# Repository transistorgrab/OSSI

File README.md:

# OSSI
Open Source Solar Inverter - Software, Hardware, Mechanics

This repository initially clones all content from the former Sourceforge hosted project site (https://sourceforge.net/projects/os-si/). Since the outages on Sourceforge became more frequent, I decided to change over to Github which seems more reliable at this time.

This project aims to build an Open Source (Software and Hardware) Solar Inverter.

The goal is to design a solar inverter with parts that are available trough common distributors with no special manufactured parts.

All documentation (software, hardware, mechanics) is open and free to use by everyone.

Solar inverters can be very complex devices to build and there is a lot to learn on the way.

Join, collaborate, learn and help make the world a better place.

The sun shines for everyone! 😊

The current activities take place in the [Wiki](https://github.com/transistorgrab/OSSI/wiki), where we collect the requirements.

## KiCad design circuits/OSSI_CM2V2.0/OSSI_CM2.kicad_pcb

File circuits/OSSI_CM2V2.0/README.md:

# O.S.S.I Control Module 2 V2.0

This version of the control module contains various improvements over version 1.0/1.1 of the module.

## Breaking Changes
### Different controller pin mapping.
This change was necessary due to an oversight when assigning pins to PWMs. Now the bridge controlling PWMs are assigned to timer 1 channel 1 and 1N and channels 2 and 2N which now implements requirement SOFT-3002.

However, the module footprint still shows the same pin mapping as before.

## Improvements
The board now features an I²C EEPROM for storage of parameters, settings, counters and other data that should be protected between firmware updates. This is an actual EEPROM and not a Flash due to vastly better data retention and write cycles.

The package of the 8 pin ICs on the module are now changed to TSSOP to improve use of board space.

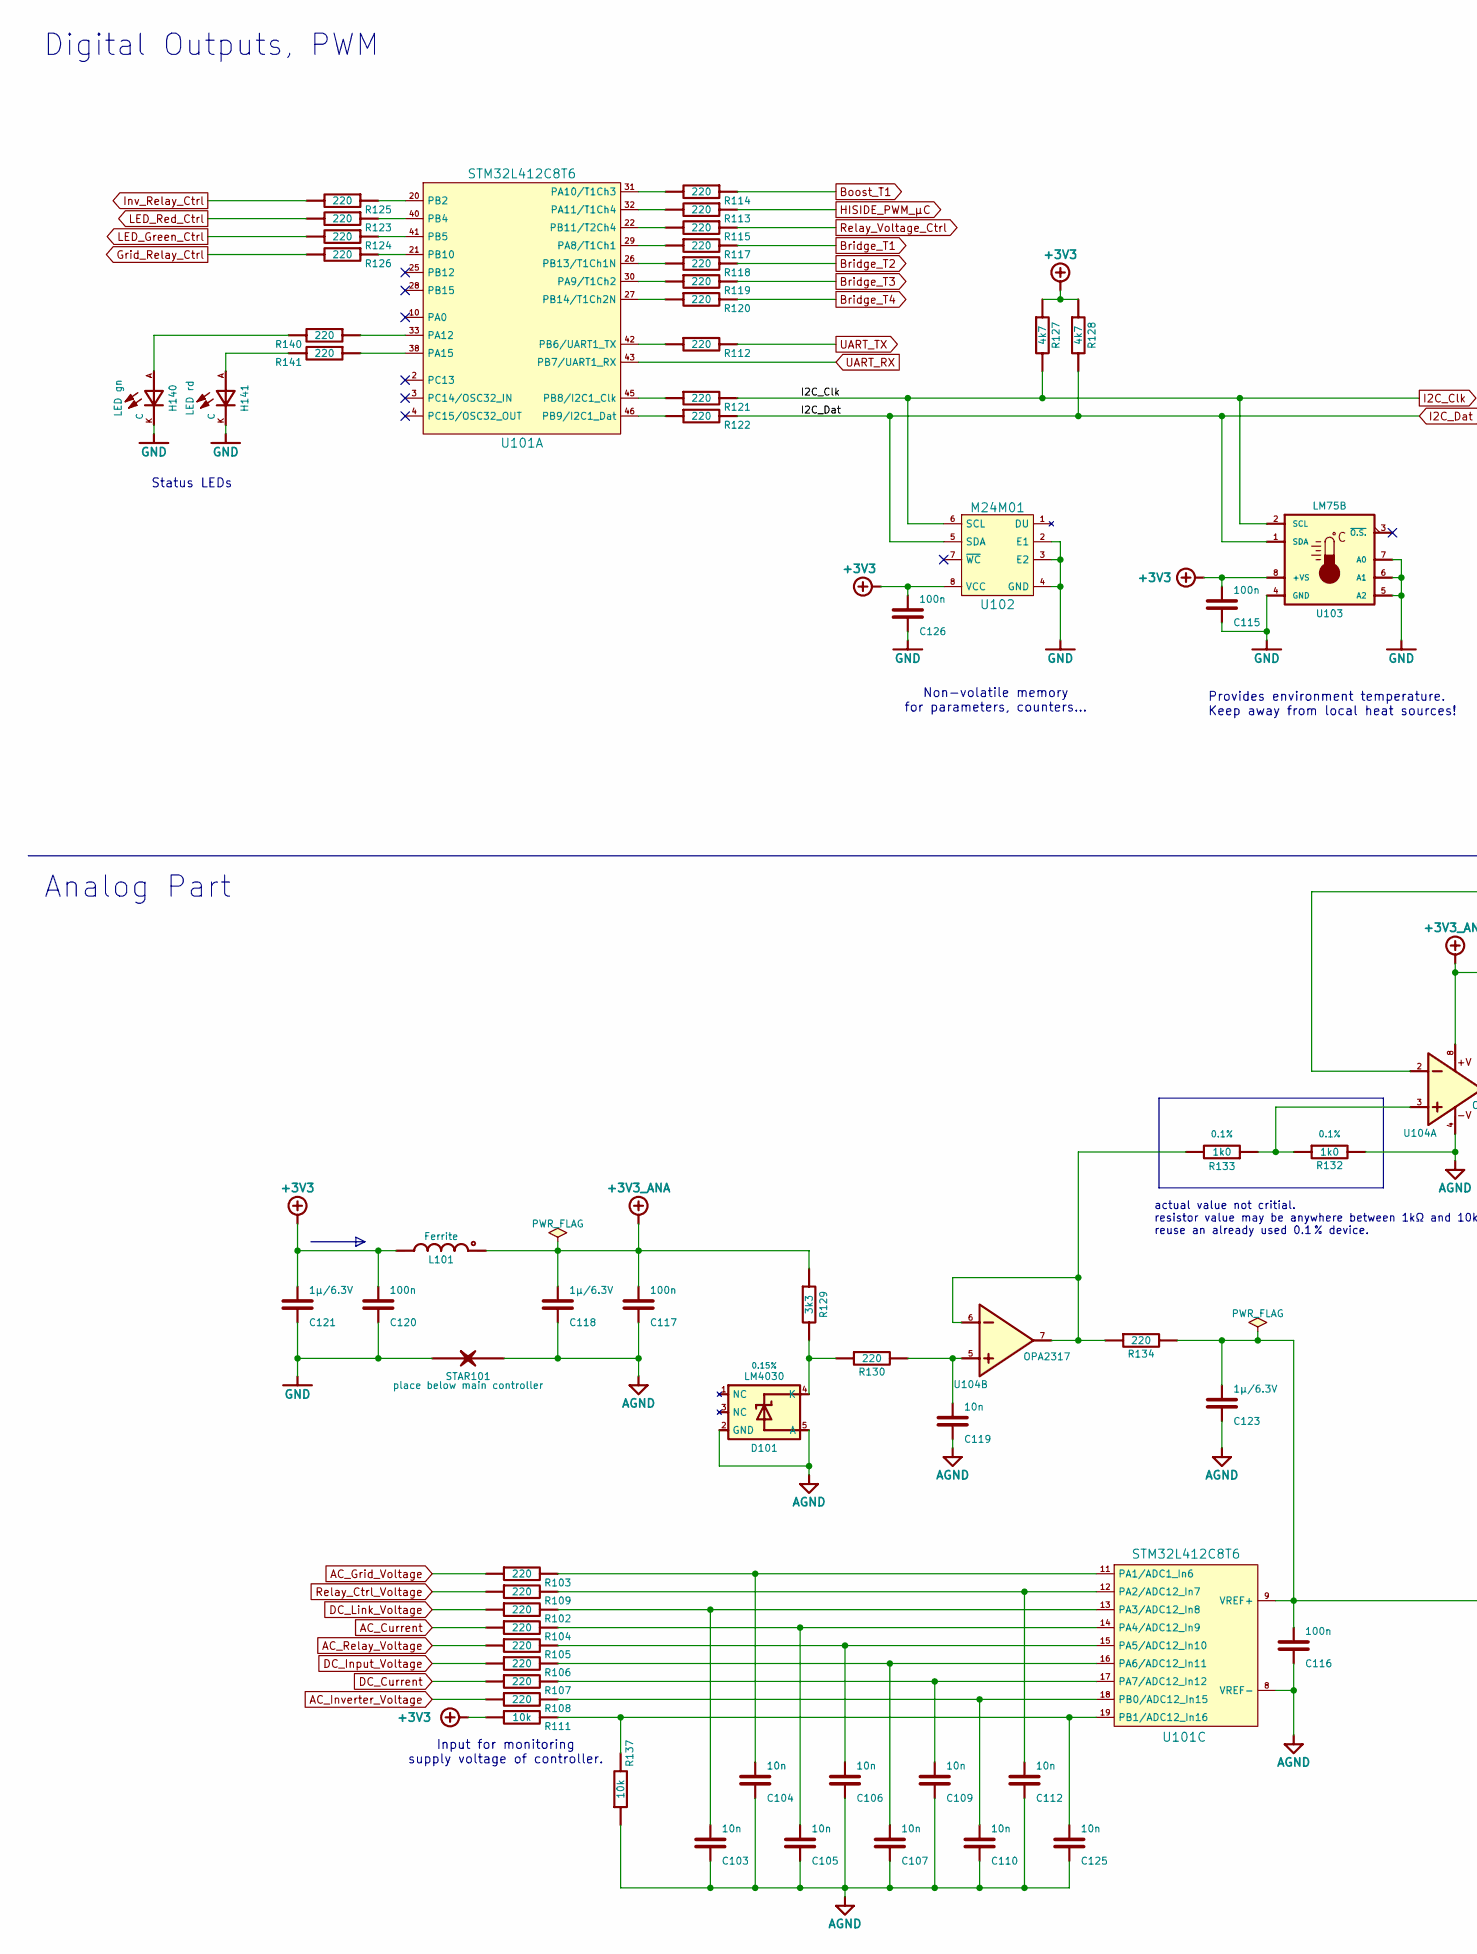
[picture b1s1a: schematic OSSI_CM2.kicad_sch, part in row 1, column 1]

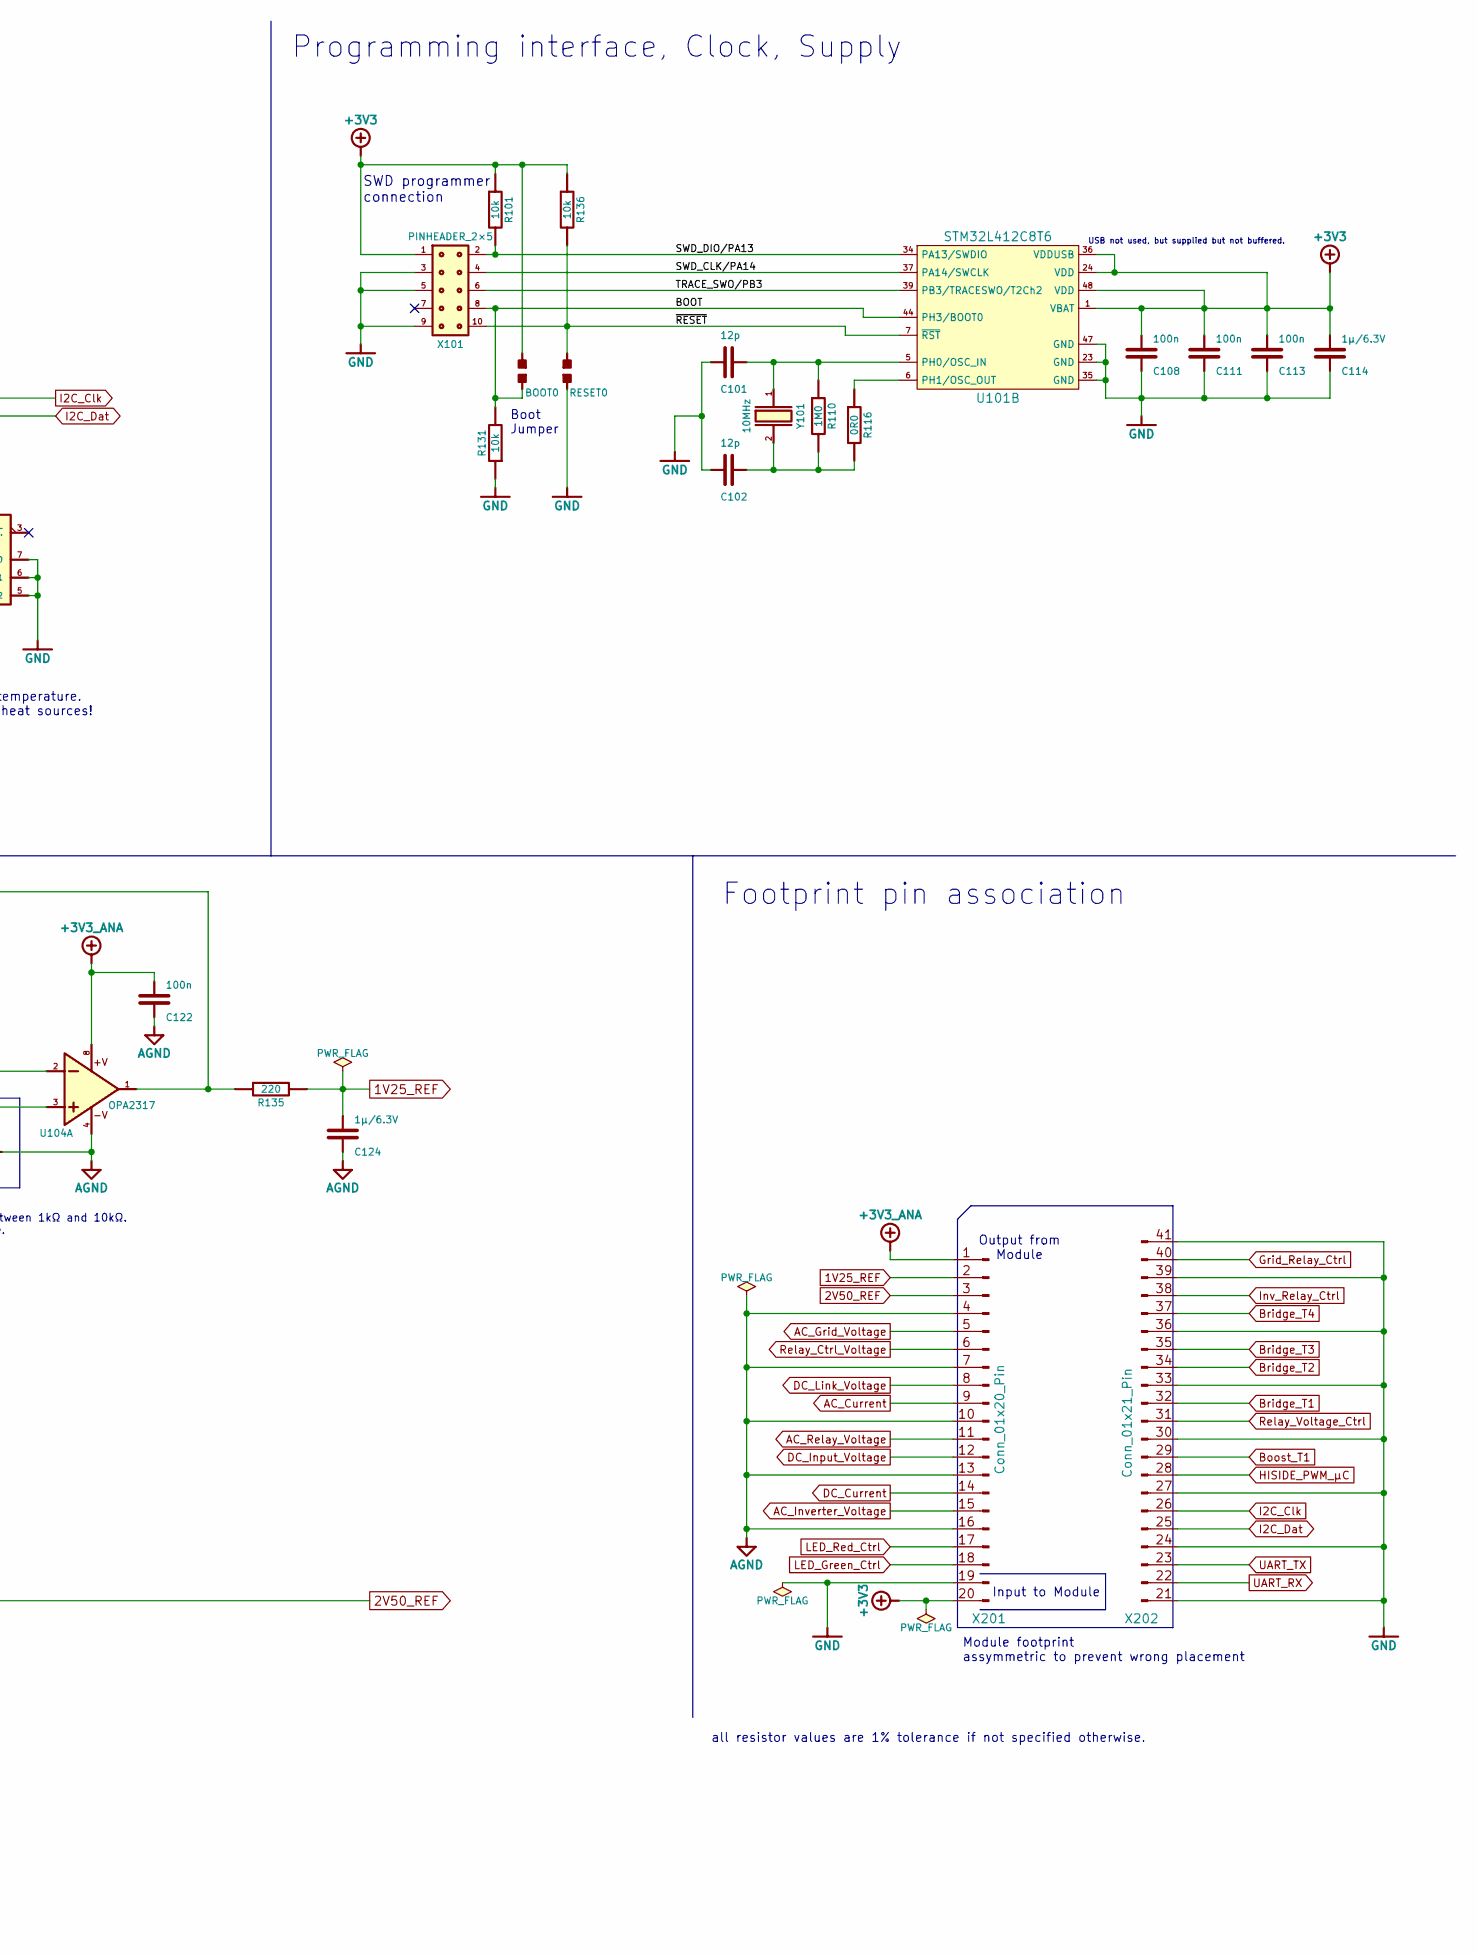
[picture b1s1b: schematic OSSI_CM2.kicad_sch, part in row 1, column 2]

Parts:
BOOT0: Solder_bridge_open; JUMPER_OPEN
C101, C102: 12p; 0603_W_C; Tolerance %; Partnumber P
C103, C104, C105, C106, C107, C109, C110, C112, C119, C125: 10n; 0603_W_C; Tolerance %; Partnumber P
C108, C111, C113, C115, C116, C117, C120, C122, C126: 100n; 0603_W_C; Tolerance %; Partnumber P
C114, C118, C121, C123, C124: 1µ/6.3V; 0805_W_C; Tolerance %; Partnumber P
D101: LM4030; SOT-23-5; Tolerance 0.15%; Partnumber P
H140: LED gn; 0603_W_LED; Partnumber P
H141: LED rd; 0603_W_LED; Partnumber P
L101: Ferrite; 0805_W_L; Partnumber P
R101, R111, R131, R136, R137: 10k; 0603_W_R; Tolerance %; Partnumber P
R102, R103, R104, R105, R106, R107, R108, R109, R112, R113, R114, R115, R117, R118, R119, R120, R121, R122, R123, R124, R125, R126, R130, R134, R135, R140, R141: 220; 0603_W_R; Tolerance %; Partnumber P
R110: 1M0; 0603_W_R; Tolerance %; Partnumber P
R116: 0R0; 0603_W_R; Tolerance %; Partnumber P
R127, R128: 4k7; 0603_W_R; Tolerance %; Partnumber P
R129: 3k3; 0603_W_R; Tolerance %; Partnumber P
R132, R133: 1k0; 0603_W_R; Tolerance 0.1%; Partnumber P
RESET0: Solder_bridge_open; JUMPER_OPEN
STAR101: STARPOINT
U101: STM32L412C8T6; LQFP-48_7x7mm_P0.5mm
U102: M24M01; TSSOP8
U103: LM75B; TSSOP8
U104: OPA2317; TSSOP8; Partnumber P
X101: PINHEADER_2×5; PinHeader_2x05_P2.54mm_Vertical; Partnumber P
X201: Conn_01x20_Pin; PinHeader_1x20_P2.54mm_Vertical
X202: Conn_01x21_Pin; PinHeader_1x21_P2.54mm_Vertical
Y101: 10MHz; HC49_US; Partnumber P

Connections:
1V25_REF: C124.2, R135.2, X201.2
2V50_REF: C116.2, C123.2, R134.2, U101.9 (VREF+), X201.3
+3V3: BOOT0.1, C108.2, C111.2, C113.2, C114.2, C115.2, C120.2, C121.2, C126.2, L101.2, R101.1, R111.1, R127.1, R128.1, R136.1, U101.1 (VBAT), U101.24 (VDD), U101.36 (VDDUSB), U101.48 (VDD), U102.8 (VCC), U103.8 (+VS), X101.1, X201.20
+3V3_ANA: C117.2, C118.2, C122.2, L101.1, R129.1, U104.8, X201.1
/BOOT: BOOT0.2, R131.2, U101.44 (PH3/BOOT0), X101.8
/SWD_CLK/PA14: U101.37 (PA14/SWCLK), X101.4
/SWD_DIO/PA13: R101.2, U101.34 (PA13/SWDIO), X101.2
/TRACE_SWO/PB3: U101.39 (PB3/TRACESWO/T2Ch2), X101.6
/~RESET: R136.2, RESET0.2, U101.7 (~RST), X101.10
AC_Current: R104.1, X201.9
AC_Grid_Voltage: R103.1, X201.5
AC_Inverter_Voltage: R108.1, X201.15
AC_Relay_Voltage: R105.1, X201.11
AGND: C103.1, C104.1, C105.1, C106.1, C107.1, C109.1, C110.1, C112.1, C116.1, C117.1, C118.1, C119.1, C122.1, C123.1, C124.1, C125.1, D101.2 (GND), D101.5 (A), R132.2, R137.1, STAR101.1, U101.8 (VREF-), U104.4, X201.4, X201.7, X201.10, X201.13, X201.16
Boost_T1: R114.1, X202.29
Bridge_T1: R117.2, X202.32
Bridge_T2: R118.2, X202.34
Bridge_T3: R119.2, X202.35
Bridge_T4: R120.2, X202.37
DC_Current: R107.1, X201.14
DC_Input_Voltage: R106.1, X201.12
DC_Link_Voltage: R102.1, X201.8
GND: C101.1, C102.1, C108.1, C111.1, C113.1, C114.1, C115.1, C120.1, C121.1, C126.1, H140.K, H141.K, R131.1, RESET0.1, STAR101.2, U101.23 (GND), U101.35 (GND), U101.47 (GND), U102.2 (E1), U102.3 (E2), U102.4 (GND), U103.4 (GND), U103.5 (A2), U103.6 (A1), U103.7 (A0), X101.3, X101.5, X101.9, X201.19, X202.21, X202.24, X202.27, X202.30, X202.33, X202.36, X202.39, X202.41
Grid_Relay_Ctrl: R126.2, X202.40
HISIDE_PWM_µC: R113.1, X202.28
I2C_Clk: R121.2, R127.2, U102.6 (SCL), U103.2 (SCL), X202.26
I2C_Dat: R122.2, R128.2, U102.5 (SDA), U103.1 (SDA), X202.25
Inv_Relay_Ctrl: R125.2, X202.38
LED_Green_Ctrl: R124.2, X201.18
LED_Red_Ctrl: R123.2, X201.17
unnamed: C102.2, R110.2, R116.2, Y101.2
unnamed: C119.2, R130.2, U104.5
unnamed: D101.4 (K), R129.2, R130.1
unnamed: H140.A, R140.2
unnamed: H141.A, R141.2
unnamed: R132.1, R133.1, U104.3
unnamed: R133.2, R134.1, U104.6, U104.7
unnamed: R135.1, U104.1, U104.2
unnamed: R117.1, U101.29 (PA8/T1Ch1)
unnamed: R119.1, U101.30 (PA9/T1Ch2)
unnamed: R114.2, U101.31 (PA10/T1Ch3)
unnamed: R113.2, U101.32 (PA11/T1Ch4)
unnamed: R140.1, U101.33 (PA12)
unnamed: R141.1, U101.38 (PA15)
unnamed: R125.1, U101.20 (PB2)
unnamed: R123.1, U101.40 (PB4)
unnamed: R124.1, U101.41 (PB5)
unnamed: R112.1, U101.42 (PB6/UART1_TX)
unnamed: R121.1, U101.45 (PB8/I2C1_Clk)
unnamed: R122.1, U101.46 (PB9/I2C1_Dat)
unnamed: R126.1, U101.21 (PB10)
unnamed: R115.2, U101.22 (PB11/T2Ch4)
unnamed: R118.1, U101.26 (PB13/T1Ch1N)
unnamed: R120.1, U101.27 (PB14/T1Ch2N)
unnamed: C101.2, R110.1, U101.5 (PH0/OSC_IN), Y101.1
unnamed: R116.1, U101.6 (PH1/OSC_OUT)
unnamed: C104.2, R103.2, U101.11 (PA1/ADC1_In6)
unnamed: C112.2, R109.2, U101.12 (PA2/ADC12_In7)
unnamed: C103.2, R102.2, U101.13 (PA3/ADC12_In8)
unnamed: C105.2, R104.2, U101.14 (PA4/ADC12_In9)
unnamed: C106.2, R105.2, U101.15 (PA5/ADC12_In10)
unnamed: C107.2, R106.2, U101.16 (PA6/ADC12_In11)
unnamed: C109.2, R107.2, U101.17 (PA7/ADC12_In12)
unnamed: C110.2, R108.2, U101.18 (PB0/ADC12_In15)
unnamed: C125.2, R111.2, R137.2, U101.19 (PB1/ADC12_In16)
Relay_Ctrl_Voltage: R109.1, X201.6
Relay_Voltage_Ctrl: R115.1, X202.31
UART_RX: U101.43 (PB7/UART1_RX), X202.22
UART_TX: R112.2, X202.23

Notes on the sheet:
SWD programmer connection
Provides environment temperature. Keep away from local heat sources!
Analog Part
Output from Module
Footprint pin association
Input for monitoring supply voltage of controller.
Programming interface, Clock, Supply
USB not used, but supplied but not buffered.
Module footprint assymmetric to prevent wrong placement
Input to Module
Digital Outputs, PWM
Status LEDs
Boot Jumper
all resistor values are 1% tolerance if not specified otherwise.
Non-volatile memory for parameters, counters…
actual value not critial. resistor value may be anywhere between 1kΩ and 10kΩ. reuse an already used 0.1 % device.

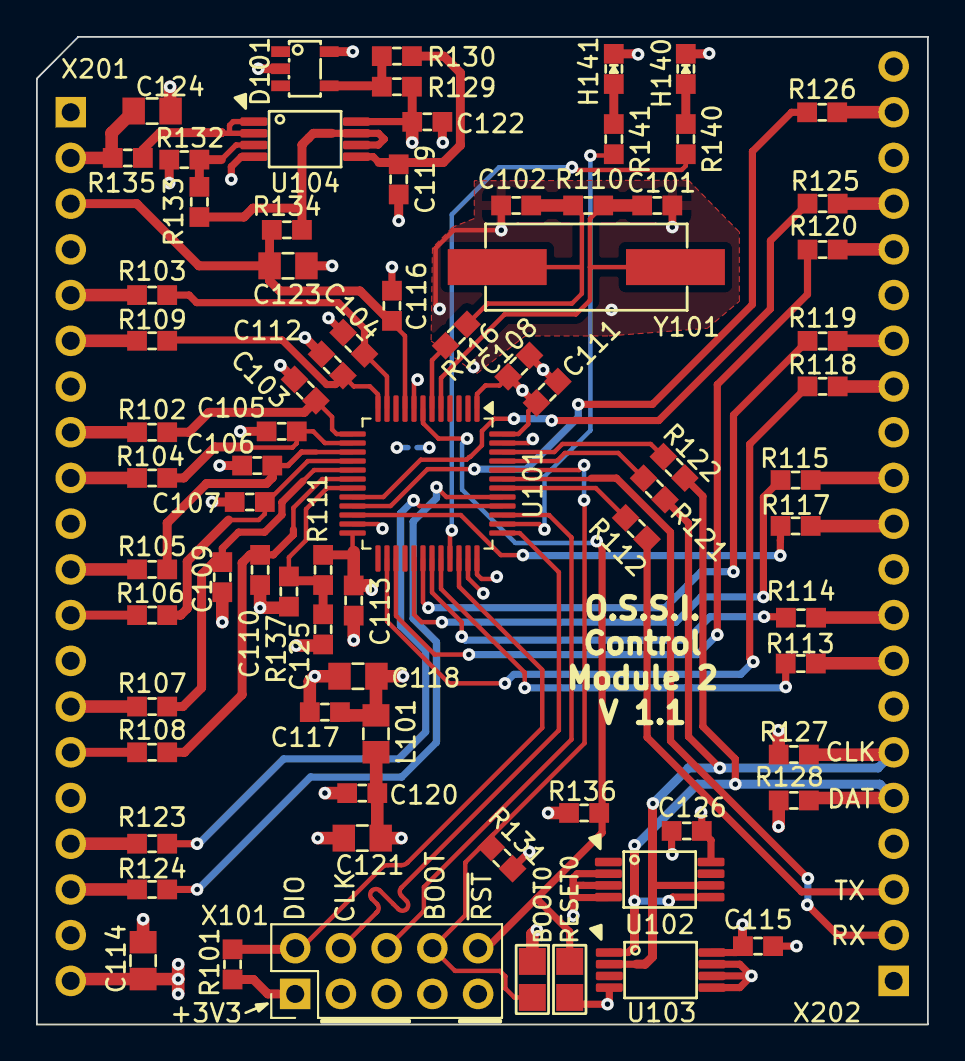
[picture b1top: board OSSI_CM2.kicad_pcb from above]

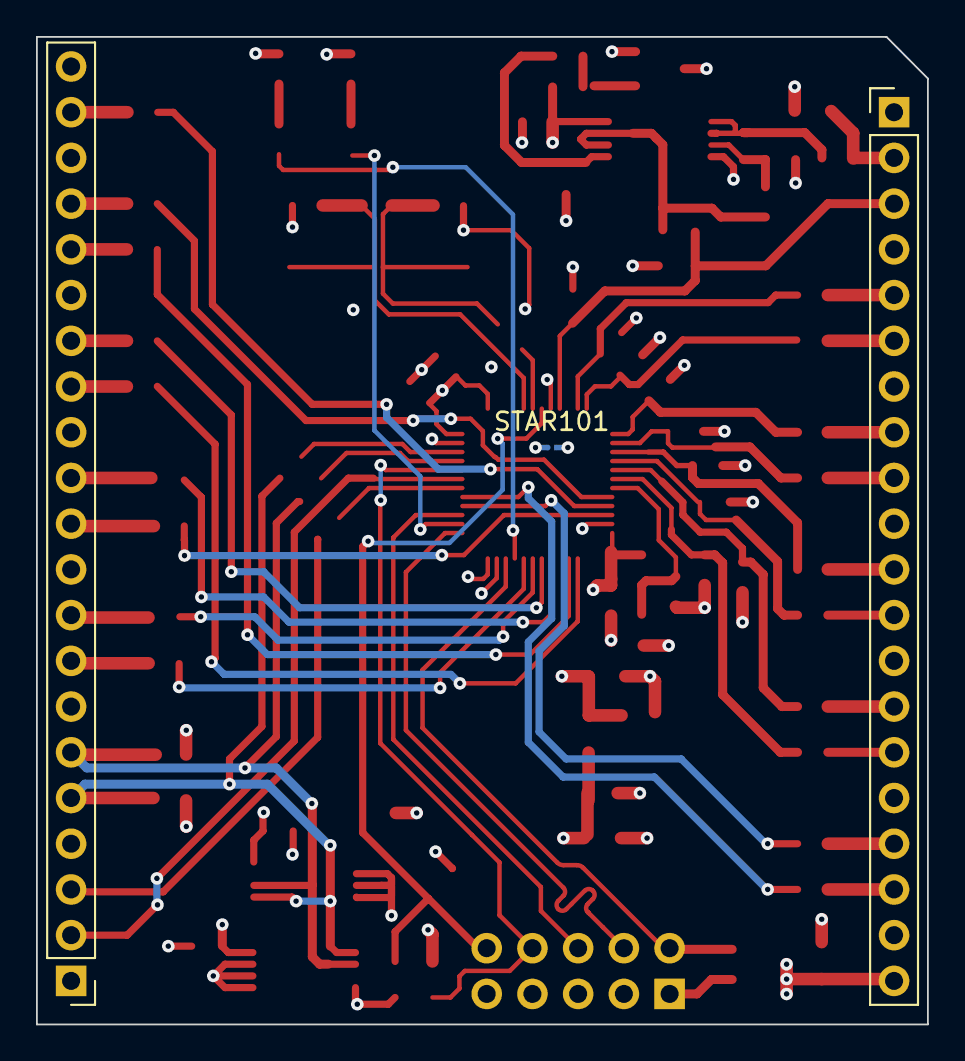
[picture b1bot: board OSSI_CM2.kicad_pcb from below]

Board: 4 copper layers, 49.5 x 54.9 mm, 80 parts (3 on the bottom side), 69 nets.

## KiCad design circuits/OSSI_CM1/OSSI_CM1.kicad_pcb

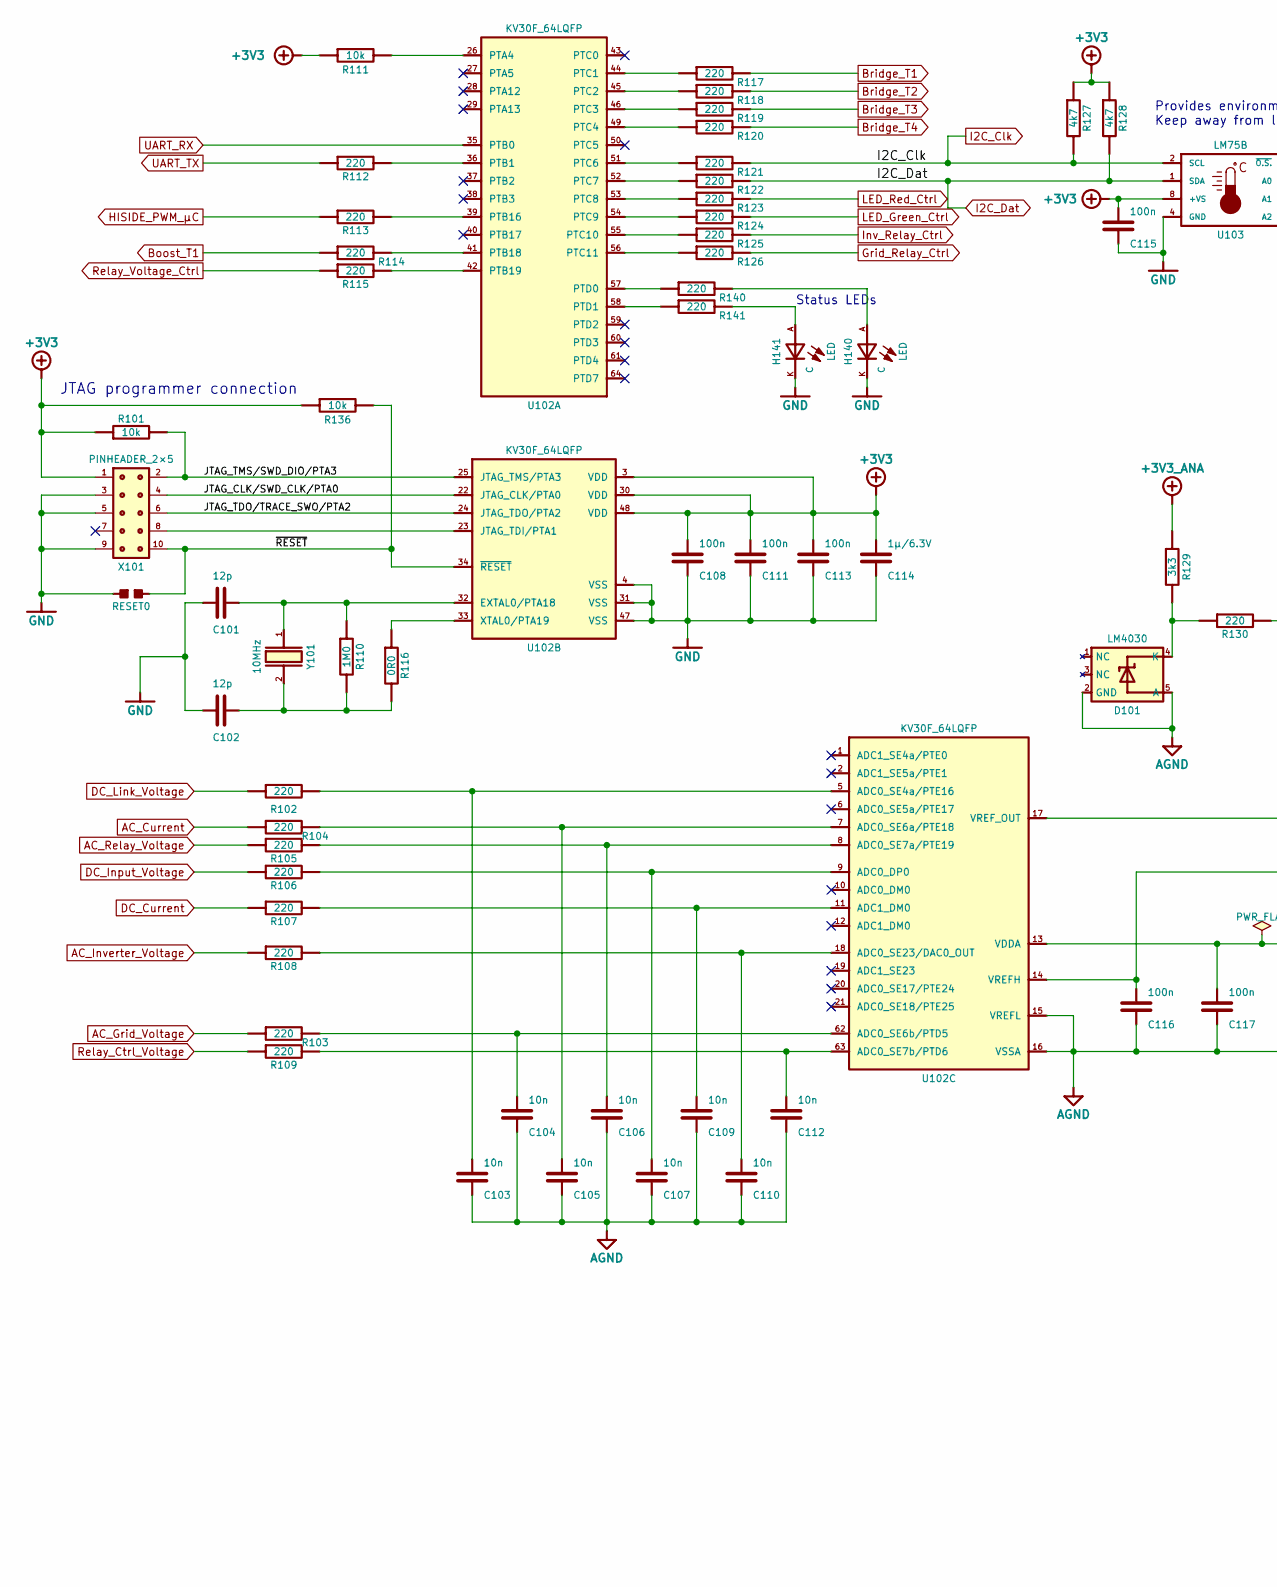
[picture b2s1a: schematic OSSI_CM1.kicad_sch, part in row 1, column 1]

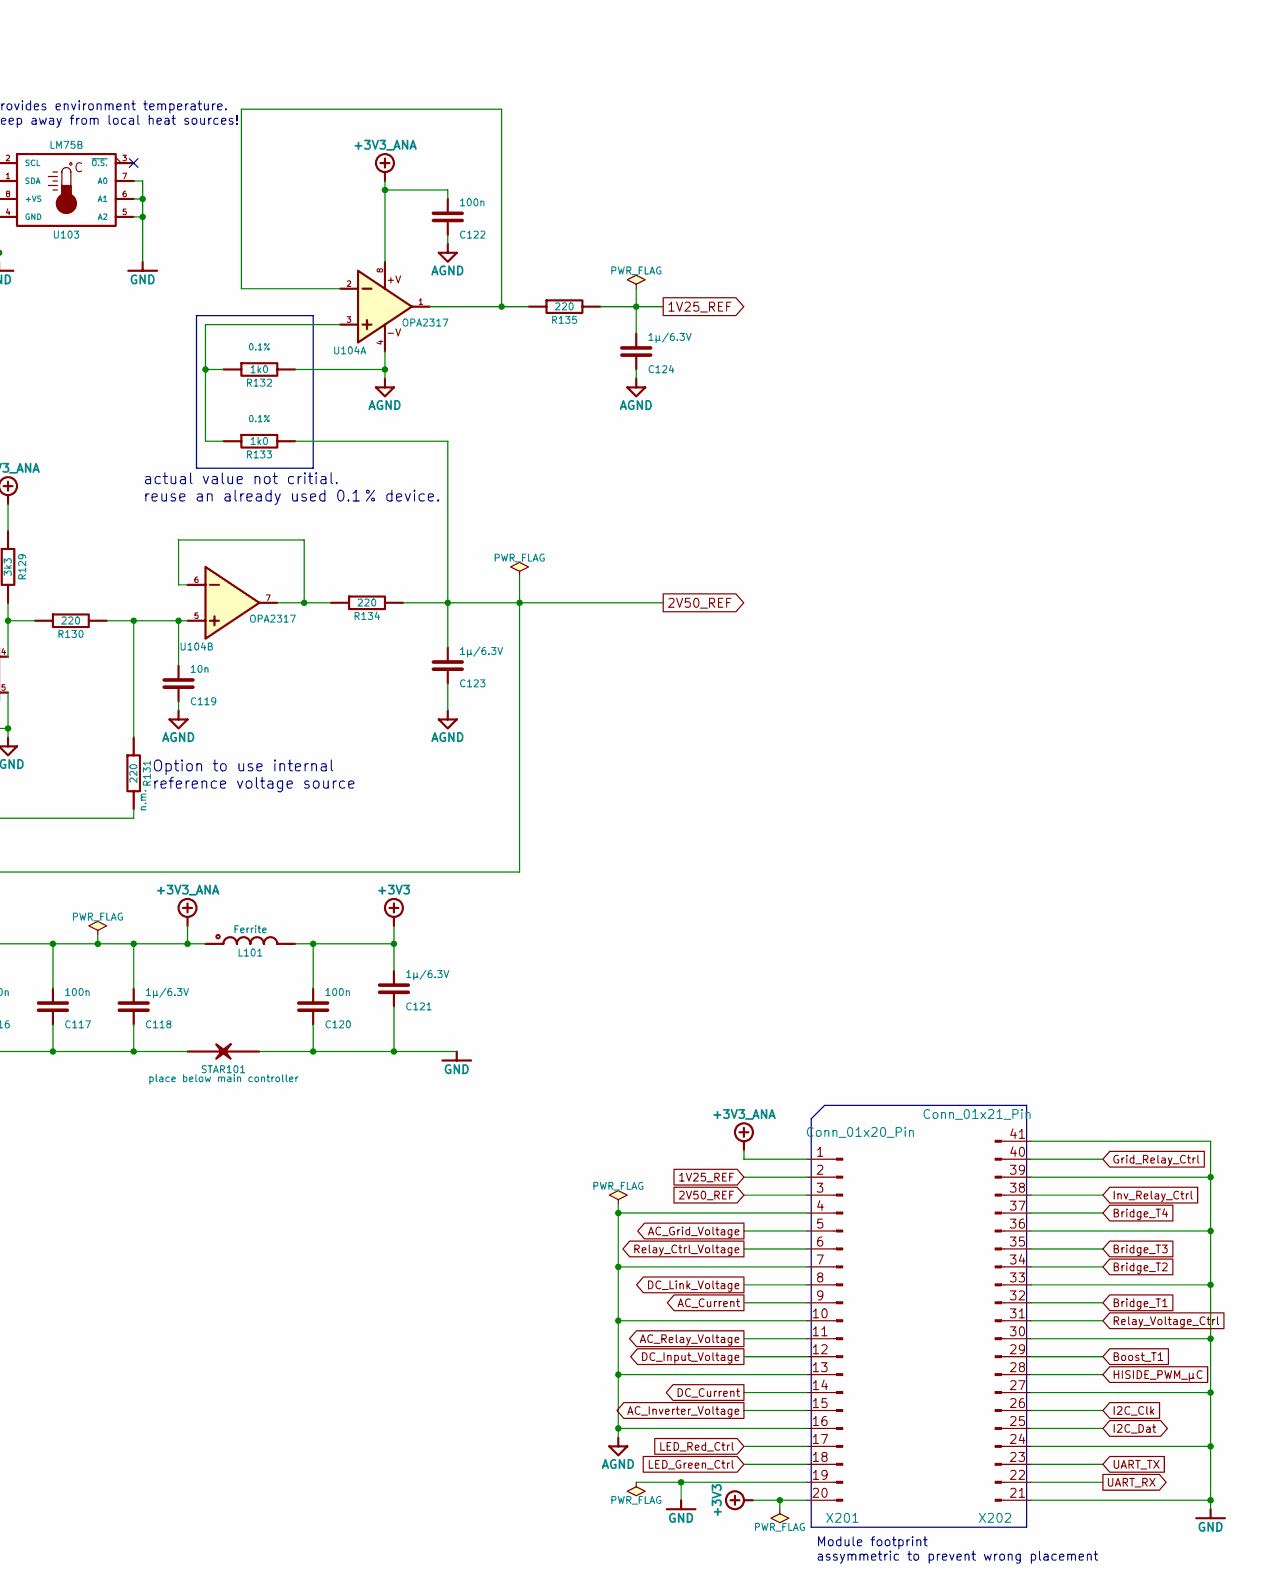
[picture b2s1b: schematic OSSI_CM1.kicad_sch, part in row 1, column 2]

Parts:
C101, C102: 12p; 0603_W; Tolerance %; Partnumber P
C103, C104, C105, C106, C107, C109, C110, C112, C119: 10n; 0603_W; Tolerance %; Partnumber P
C108, C111, C113, C115, C116, C117, C120, C122: 100n; 0603_W; Tolerance %; Partnumber P
C114, C118, C121, C123, C124: 1µ/6.3V; 0805_W; Tolerance %; Partnumber P
D101: LM4030; SOT-23-5; Partnumber P
H140, H141: LED; 0603_W_LED; Partnumber P
L101: Ferrite; 0805_W; Partnumber P
R101, R111, R136: 10k; 0603_W; Tolerance %; Partnumber P
R102, R103, R104, R105, R106, R107, R108, R109, R112, R113, R114, R115, R117, R118, R119, R120, R121, R122, R123, R124, R125, R126, R130, R131, R134, R135, R140, R141: 220; 0603_W; Tolerance %; Partnumber P
R110: 1M0; 0603_W; Tolerance %; Partnumber P
R116: 0R0; 0603_W; Tolerance %; Partnumber P
R127, R128: 4k7; 0603_W; Tolerance %; Partnumber P
R129: 3k3; 0603_W; Tolerance %; Partnumber P
R132, R133: 1k0; 0603_W; Tolerance 0.1%; Partnumber P
RESET0: Solder_bridge_open; JUMPER_OPEN
STAR101: STARPOINT
U102: KV30F_64LQFP; LQFP-64_10x10_Pitch0.5mm; Partnumber P
U103: LM75B; SOIC8
U104: OPA2317; SOIC8; Partnumber P
X101: PINHEADER_2×5; PinHeader_2x05_P2.54mm_Vertical; Partnumber P
X201: Conn_01x20_Pin; PinHeader_1x20_P2.54mm_Vertical
X202: Conn_01x21_Pin; PinHeader_1x21_P2.54mm_Vertical
Y101: 10MHz; HC49_US; Partnumber P

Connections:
1V25_REF: C124.2, R135.2, X201.2
2V50_REF: C116.2, C123.2, R133.2, R134.2, U102.14 (VREFH), X201.3
+3V3: C108.2, C111.2, C113.2, C114.2, C115.2, C120.2, C121.2, L101.2, R101.1, R111.1, R127.1, R128.1, R136.1, U102.3 (VDD), U102.30 (VDD), U102.48 (VDD), U103.8 (+VS), X101.1, X201.20
+3V3_ANA: C117.2, C118.2, C122.2, L101.1, R129.1, U102.13 (VDDA), U104.8, X201.1
/JTAG_CLK/SWD_CLK/PTA0: U102.22 (JTAG_CLK/PTA0), X101.4
/JTAG_TDO/TRACE_SWO/PTA2: U102.24 (JTAG_TDO/PTA2), X101.6
/JTAG_TMS/SWD_DIO/PTA3: R101.2, U102.25 (JTAG_TMS/PTA3), X101.2
/~RESET: R136.2, RESET0.2, U102.34 (~RESET), X101.10
AC_Current: R104.1, X201.9
AC_Grid_Voltage: R103.1, X201.5
AC_Inverter_Voltage: R108.1, X201.15
AC_Relay_Voltage: R105.1, X201.11
AGND: C103.1, C104.1, C105.1, C106.1, C107.1, C109.1, C110.1, C112.1, C116.1, C117.1, C118.1, C119.1, C122.1, C123.1, C124.1, D101.2 (GND), D101.5 (A), R132.2, STAR101.1, U102.15 (VREFL), U102.16 (VSSA), U104.4, X201.4, X201.7, X201.10, X201.13, X201.16
Boost_T1: R114.1, X202.29
Bridge_T1: R117.2, X202.32
Bridge_T2: R118.2, X202.34
Bridge_T3: R119.2, X202.35
Bridge_T4: R120.2, X202.37
DC_Current: R107.1, X201.14
DC_Input_Voltage: R106.1, X201.12
DC_Link_Voltage: R102.1, X201.8
GND: C101.1, C102.1, C108.1, C111.1, C113.1, C114.1, C115.1, C120.1, C121.1, H140.K, H141.K, RESET0.1, STAR101.2, U102.4 (VSS), U102.31 (VSS), U102.47 (VSS), U103.4 (GND), U103.5 (A2), U103.6 (A1), U103.7 (A0), X101.3, X101.5, X101.9, X201.19, X202.21, X202.24, X202.27, X202.30, X202.33, X202.36, X202.39, X202.41
Grid_Relay_Ctrl: R126.2, X202.40
HISIDE_PWM_µC: R113.1, X202.28
I2C_Clk: R121.2, R127.2, U103.2 (SCL), X202.26
I2C_Dat: R122.2, R128.2, U103.1 (SDA), X202.25
Inv_Relay_Ctrl: R125.2, X202.38
LED_Green_Ctrl: R124.2, X201.18
LED_Red_Ctrl: R123.2, X201.17
unnamed: C102.2, R110.2, R116.2, Y101.2
unnamed: C109.2, R107.2, U102.11 (ADC1_DM0)
unnamed: C119.2, R130.2, R131.1, U104.5
unnamed: D101.4 (K), R129.2, R130.1
unnamed: H140.A, R140.2
unnamed: H141.A, R141.2
unnamed: R132.1, R133.1, U104.3
unnamed: R134.1, U104.6, U104.7
unnamed: R135.1, U104.1, U104.2
unnamed: R111.2, U102.26 (PTA4)
unnamed: R112.2, U102.36 (PTB1)
unnamed: R113.2, U102.39 (PTB16)
unnamed: R114.2, U102.41 (PTB18)
unnamed: R115.2, U102.42 (PTB19)
unnamed: R117.1, U102.44 (PTC1)
unnamed: R118.1, U102.45 (PTC2)
unnamed: R119.1, U102.46 (PTC3)
unnamed: R120.1, U102.49 (PTC4)
unnamed: R121.1, U102.51 (PTC6)
unnamed: R122.1, U102.52 (PTC7)
unnamed: R123.1, U102.53 (PTC8)
unnamed: R124.1, U102.54 (PTC9)
unnamed: R125.1, U102.55 (PTC10)
unnamed: R126.1, U102.56 (PTC11)
unnamed: R140.1, U102.57 (PTD0)
unnamed: R141.1, U102.58 (PTD1)
unnamed: C101.2, R110.1, U102.32 (EXTAL0/PTA18), Y101.1
unnamed: U102.23 (JTAG_TDI/PTA1), X101.8
unnamed: R116.1, U102.33 (XTAL0/PTA19)
unnamed: C107.2, R106.2, U102.9 (ADC0_DP0)
unnamed: C103.2, R102.2, U102.5 (ADC0_SE4a/PTE16)
unnamed: C105.2, R104.2, U102.7 (ADC0_SE6a/PTE18)
unnamed: C104.2, R103.2, U102.62 (ADC0_SE6b/PTD5)
unnamed: C106.2, R105.2, U102.8 (ADC0_SE7a/PTE19)
unnamed: C112.2, R109.2, U102.63 (ADC0_SE7b/PTD6)
unnamed: C110.2, R108.2, U102.18 (ADC0_SE23/DAC0_OUT)
unnamed: R131.2, U102.17 (VREF_OUT)
Relay_Ctrl_Voltage: R109.1, X201.6
Relay_Voltage_Ctrl: R115.1, X202.31
UART_RX: U102.35 (PTB0), X202.22
UART_TX: R112.1, X202.23

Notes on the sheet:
JTAG programmer connection
Provides environment temperature. Keep away from local heat sources!
Option to use internal reference voltage source
Module footprint assymmetric to prevent wrong placement
Status LEDs
actual value not critial. reuse an already used 0.1 % device.

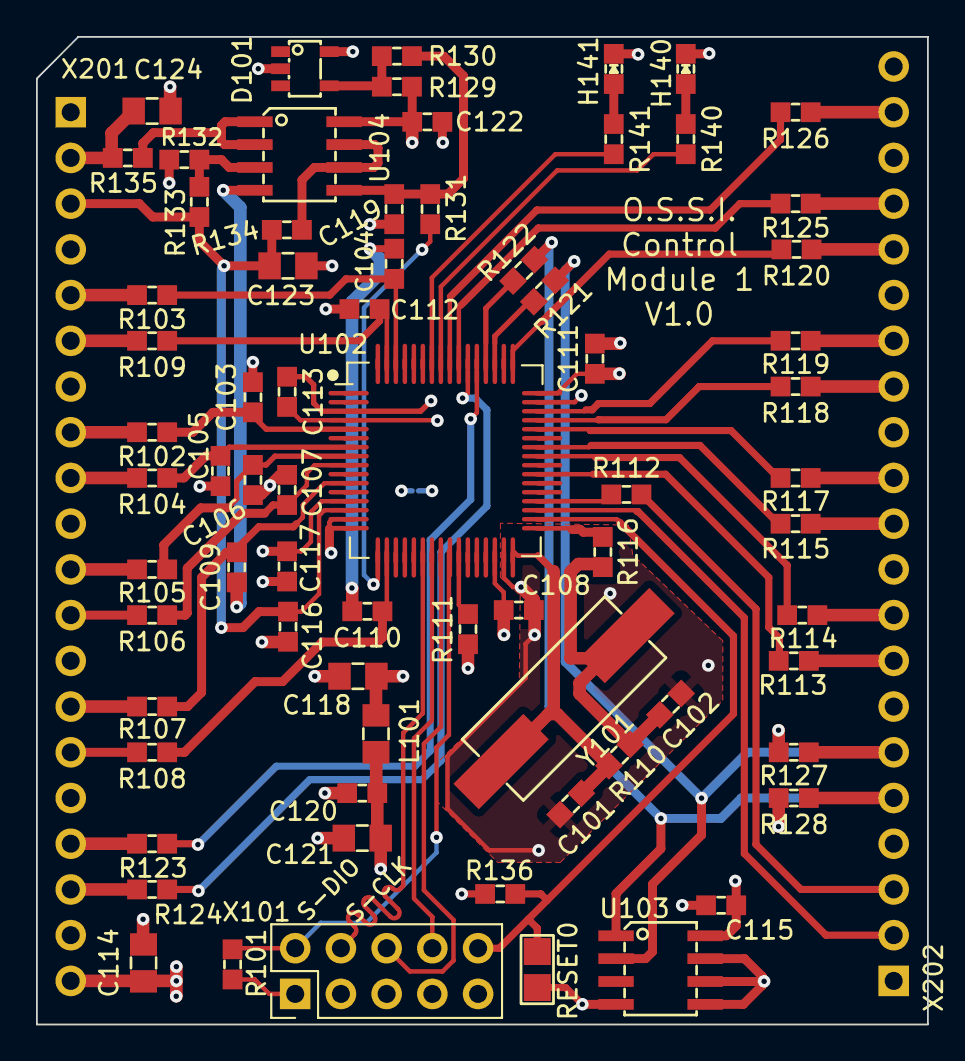
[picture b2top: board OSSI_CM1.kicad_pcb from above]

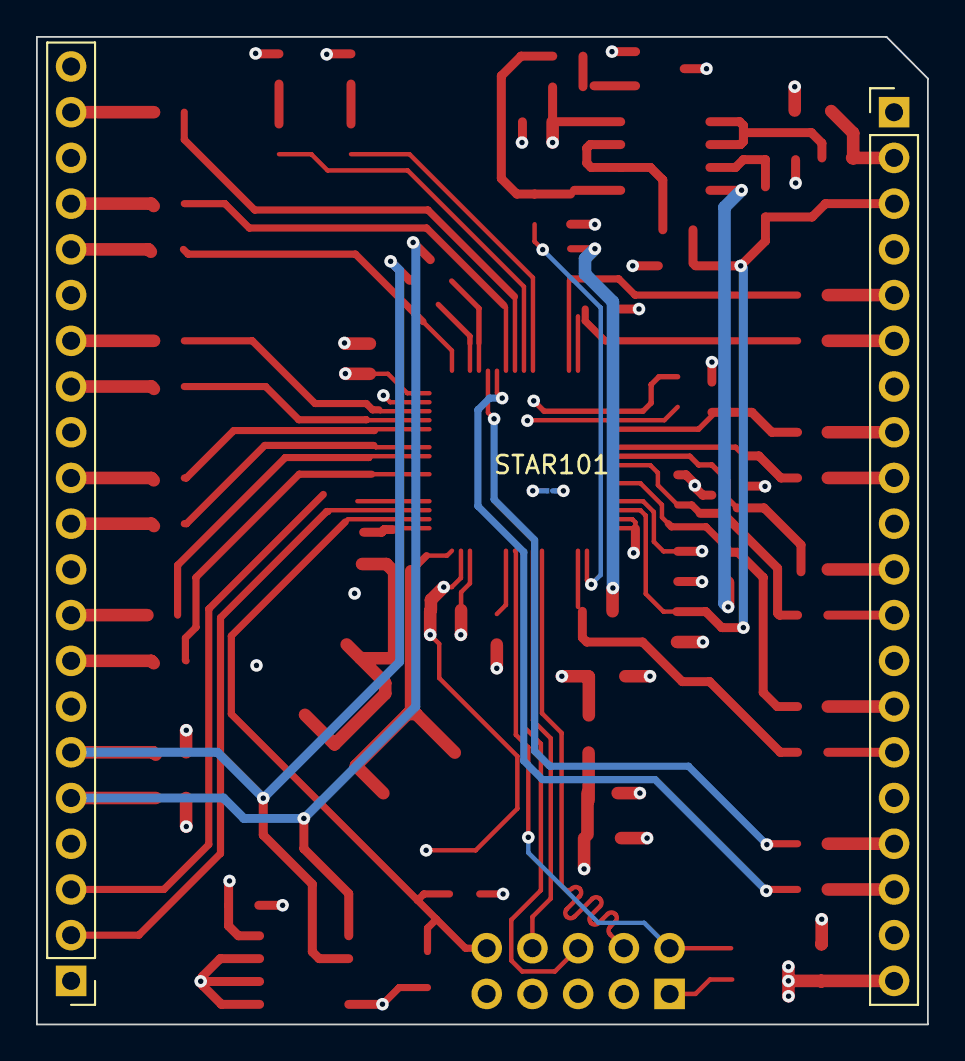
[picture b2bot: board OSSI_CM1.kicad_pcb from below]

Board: 4 copper layers, 49.5 x 54.9 mm, 75 parts (3 on the bottom side), 70 nets.

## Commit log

2016-03-03 Add images for documentation
2016-03-03 Add library for NXP KV30KV30 Kinetis controller
2016-03-06 Add project standard library, Init project schematic
2016-03-10 Add analog frontend, add needed libraries
2016-03-22 Add more circuitry, add library content
    AC current measurement
    AC filter
    AC switch
    DC booster
    DC input
    Analog frontend
2017-03-26 Updates libraries to latest Design Rules
2017-03-26 Updates all schematic pages to current components
    all components are replaced with the current component library parts
2018-04-15 fixes power symbols and pin attributes in library,
    adds various footprints
2018-08-09 adds footprints and new component libs
2019-08-31 bulk-updates libraries and schematics
    schematic is updated to Kicad 5.1.14
    updates various sheets with new circuits
    adds various component libraries
2019-12-12 updates schematics, adds high side power supply
    for inverter bridge
    adds required components to library and footprints
2021-05-25 minor updates and cleaup
2021-05-25 adds footprints
2021-11-21 small grammatic fixes
2022-10-05 Ãdds some components to standard library
2022-10-05 converts project to Kicad V6 file formats
2022-10-10 converts libraries to Kicad 6 format, updates bridge driver
2022-10-15 updates circuits, adds linear regulator NCP1117
2022-10-16 adds interface schematic and NodeMCU symbol for it
2022-10-30 adds pin headers for display options
2023-05-10 converts the project to Kicad 7
2023-11-25 adds the Control Module to the circuits
2023-11-25 add small symbol change
2023-11-25 replaces controller schematics with Control Module 1
2023-12-04 adds compute module 2 (CM2) based on STM32-L412
2024-01-04 Updates footprint paths
2024-01-21 adds fabrication files and HTML bom for easier access
2024-01-29 updates PCB with pinout comments, adds pinout PDF
2024-01-30 adds pin description for debug port
2024-02-01 adds a README.md with module summary and test report template
2024-02-02 updates pinout sheet, test report, adds calculation sheet
2024-02-03 adds version V1.1 of CM2 containing fixes vs V1.0
2024-02-03 improves code formatting, removes out-commented code
2024-02-03 improves symbol desing to prevent confusion when reading schematics
2024-02-03 adds image of 1V25_REF modification to errata
2024-02-03 adds a binary for initial operation tests
    blinks the two on-board LEDs, reads inputs for ADC1, reads temperature sensor, outputs 2 PWMs, outputs some text via UART (115200 bds).
2024-02-10 adds remark for resistor tolerances
2024-02-10 updates CM2 symbol, updates CM1 symbol, adds footprint for Control Modules
2024-02-10 exchanges control module to CM2 as default control module
2024-02-10 minor fixes to routing to several resistor pads
2024-02-10 updates the CM2 symbol with controller ports for easier reference
2024-03-04 adds control module 2.0 and required library files
2024-03-05 cleans up routing, library links, library 3D models
2024-03-06 cleans up schematic, rearranges some signals and components for better readability
2024-03-10 cleans up and rearranges schematics for more clarity
